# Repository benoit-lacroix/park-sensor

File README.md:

# Garage Parking Distance Sensor

This is my distance sensor placed in my garage for helping parking cars.

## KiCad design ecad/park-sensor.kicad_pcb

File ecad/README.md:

# `ecad` directory

There goes Electronic CAD elements such as KiCAD project files.

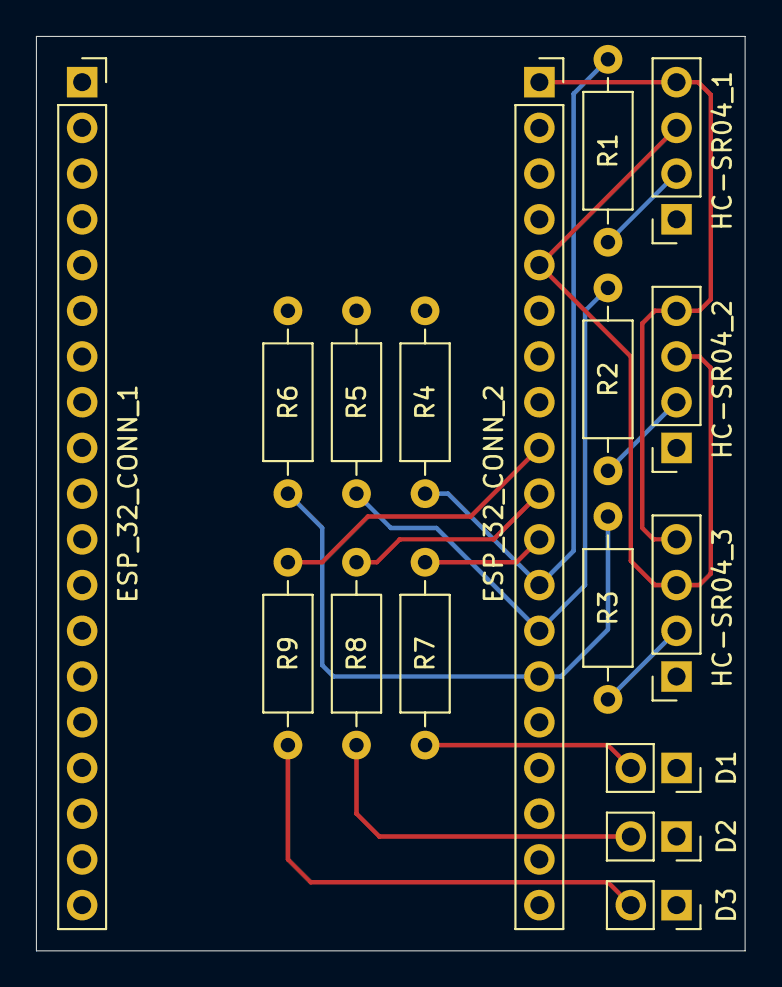
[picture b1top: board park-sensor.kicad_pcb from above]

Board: 2 copper layers, 39.4 x 50.8 mm, 17 parts (0 on the bottom side), 15 nets.

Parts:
D1: LED_GREEN; PinSocket_1x02_P2.54mm_Vertical
D2: LED_YELLOW; PinSocket_1x02_P2.54mm_Vertical
D3: LED_RED; PinSocket_1x02_P2.54mm_Vertical
ESP_32_CONN_1: ESP_32_LEFT; PinSocket_1x19_P2.54mm_Vertical
ESP_32_CONN_2: ESP_32_RIGHT; PinSocket_1x19_P2.54mm_Vertical
HC-SR04_1, HC-SR04_2, HC-SR04_3: HC-SR04; PinSocket_1x04_P2.54mm_Vertical
R1, R2, R3, R4, R5, R6: 10K; R_Axial_DIN0207_L6.3mm_D2.5mm_P10.16mm_Horizontal
R7, R8, R9: 1K; R_Axial_DIN0207_L6.3mm_D2.5mm_P10.16mm_Horizontal

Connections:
/G13: ESP_32_CONN_2.5, HC-SR04_1.3, HC-SR04_2.3, HC-SR04_3.3
/G25: ESP_32_CONN_2.11, R7.2
/G26: ESP_32_CONN_2.10, R8.2
/G27: ESP_32_CONN_2.9, R9.2
/G32: ESP_32_CONN_2.13, R2.2, R5.2
/G33: ESP_32_CONN_2.12, R1.2, R4.2
/G35: ESP_32_CONN_2.14, R3.2, R6.2
/GND: D1.1, D2.1, D3.1, ESP_32_CONN_1.13, ESP_32_CONN_1.19, ESP_32_CONN_2.6, HC-SR04_1.1, HC-SR04_2.1, HC-SR04_3.1, R4.1, R5.1, R6.1
/V5: ESP_32_CONN_2.1, HC-SR04_1.4, HC-SR04_2.4, HC-SR04_3.4
unnamed: D1.2, R7.1
unnamed: D2.2, R8.1
unnamed: D3.2, R9.1
unnamed: HC-SR04_1.2, R1.1
unnamed: HC-SR04_2.2, R2.1
unnamed: HC-SR04_3.2, R3.1

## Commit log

2021-12-23 Sketch initial commit
    Updating .gitignore
    Updating READMEs
    Adding Sketch working with 3 sensors and no lan connection
2021-12-23 Add Sketch Configuration
2021-12-23 Add KiCad Project
2021-12-23 Removing ecad Readme
2021-12-23 Correction in sketch
    Bad last distance first initialization
